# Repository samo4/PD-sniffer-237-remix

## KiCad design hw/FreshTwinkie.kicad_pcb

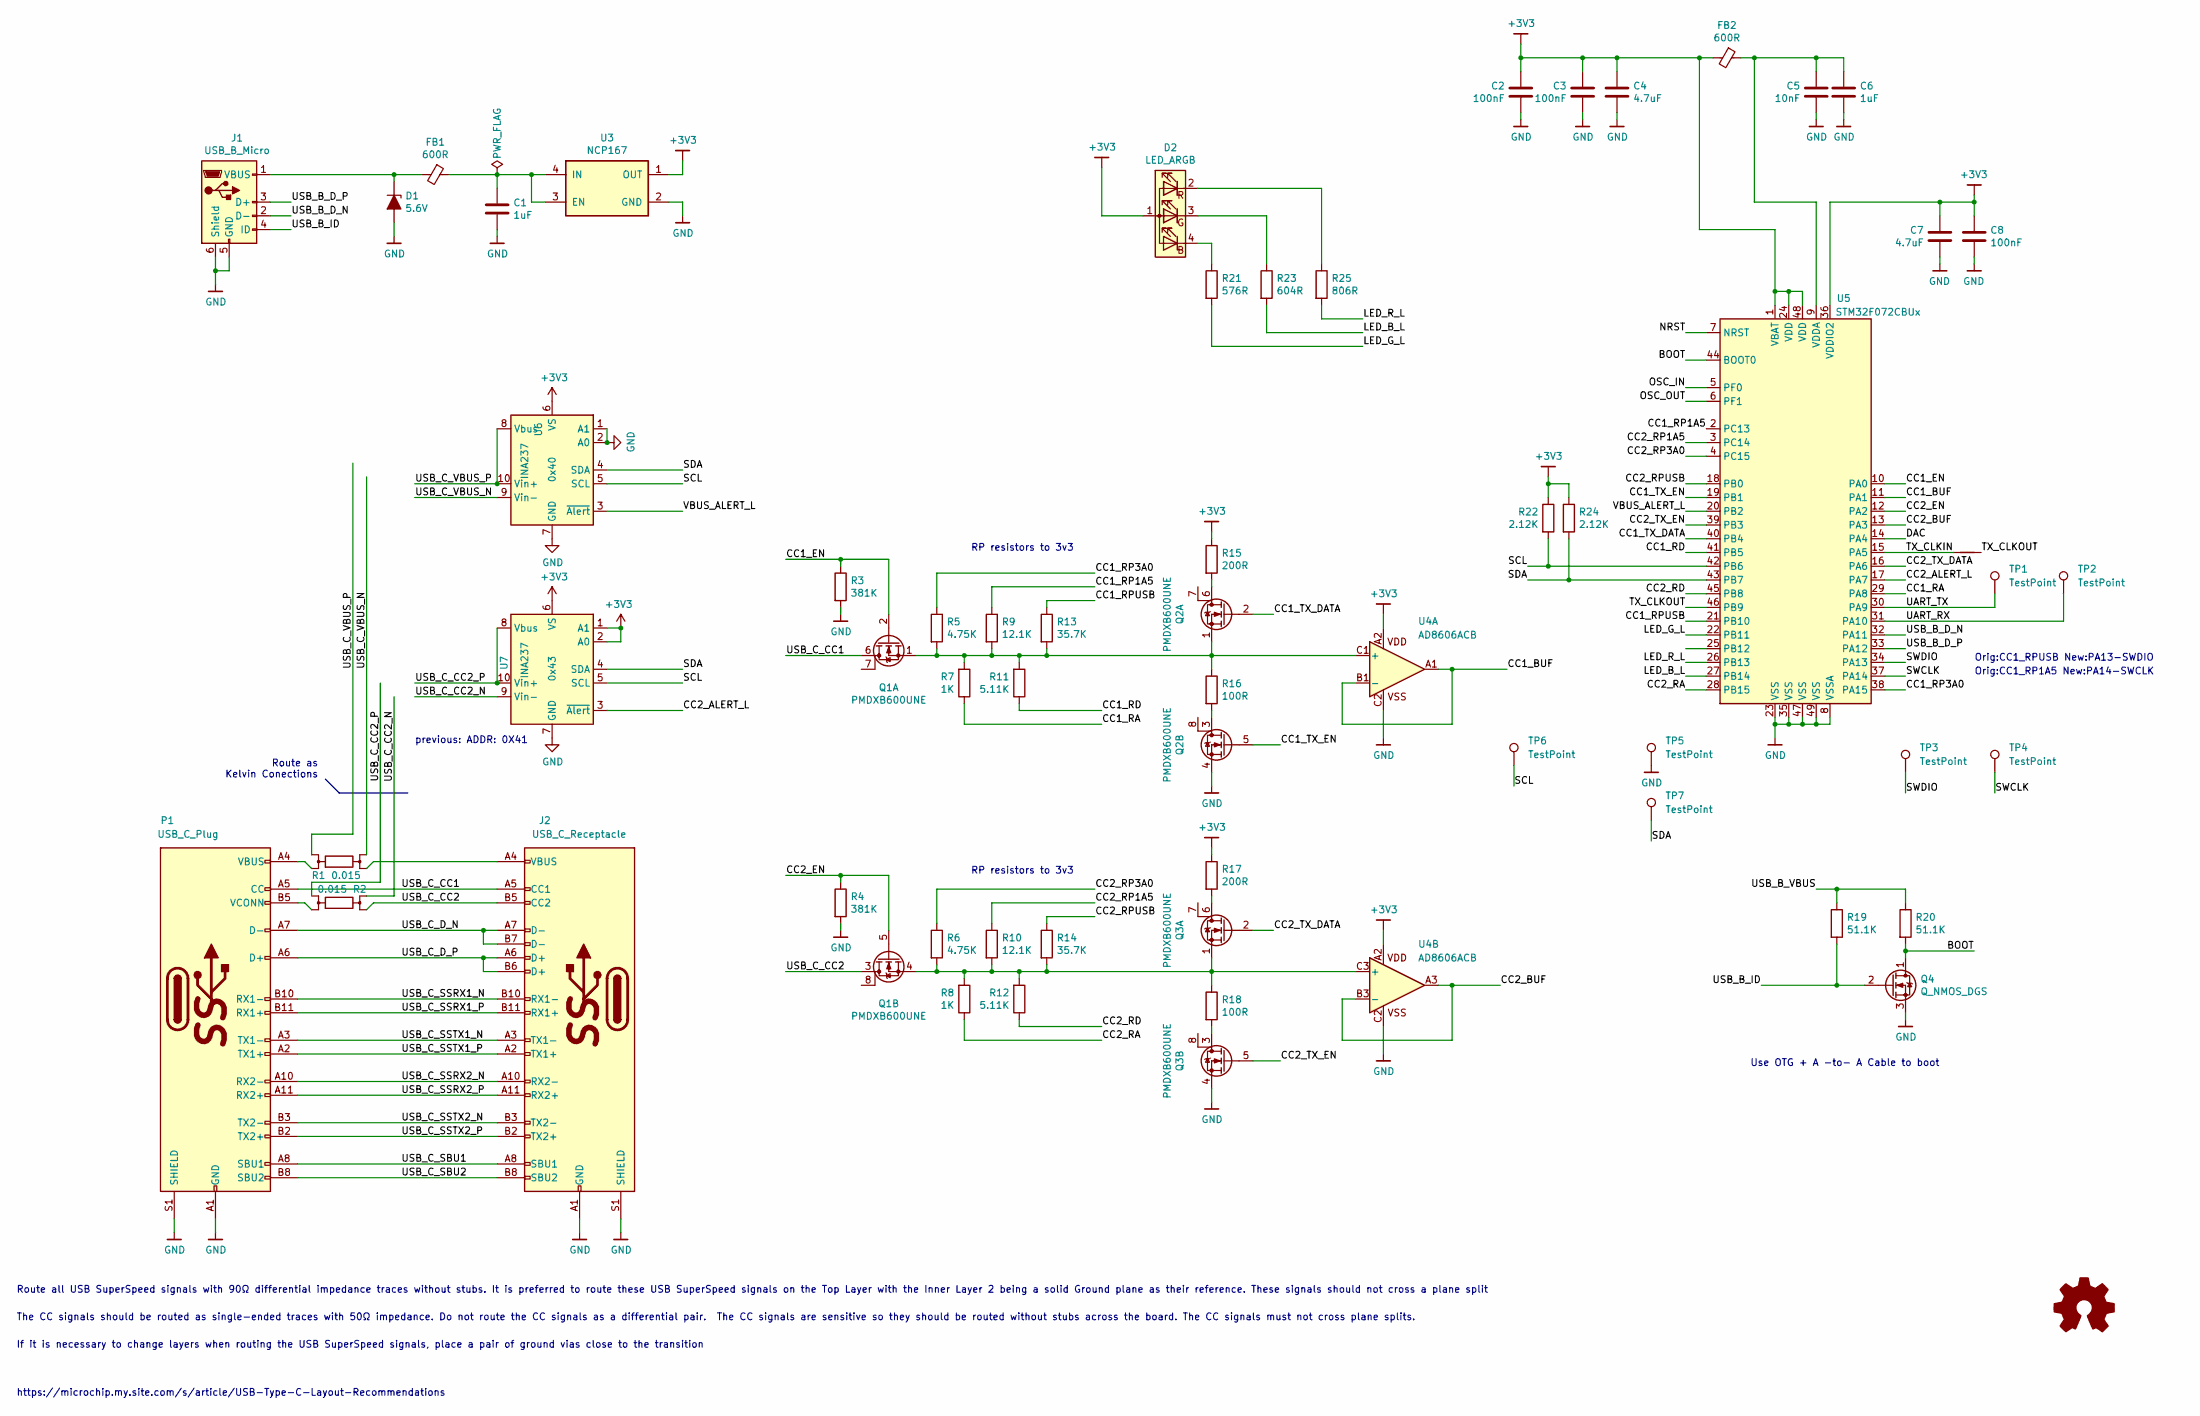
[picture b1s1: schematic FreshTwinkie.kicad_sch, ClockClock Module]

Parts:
C1, C6: 1uF; C_0402
C2, C3, C8: 100nF; C_0201
C4, C7: 4.7uF; C_0402
C5: 10nF; C_0201
D1: 5.6V; D_0402_1005Metric
D2: LED_ARGB; 0404LED_RGB
FB1, FB2: 600R; L_0402
J1: USB_B_Micro; USB_Micro-B_GCT_USB3076-30-A
J2: USB_C_Receptacle; USB_C_Receptacle_Amphenol_12401610E4-2A
NT1: Net-Tie_2; NetTie-2_SMD_Pad0.5mm
P1: USB_C_Plug; USB_C_Plug_Molex_105444
Q1, Q2, Q3: PMDXB600UNE; DFN1010B-6 (SOT1216)
Q4: Q_NMOS_DGS; MOSFET_1.0x0.6mm
R1, R2: 0.015; 4W_R_1206
R3, R4: 381K; R_0201
R5, R6: 4.75K; R_0201
R7, R8: 1K; R_0201
R9, R10: 12.1K; R_0201
R11, R12: 5.11K; R_0201
R13, R14: 35.7K; R_0201
R15, R17: 200R; R_0201
R16, R18: 100R; R_0201
R19, R20: 51.1K; R_0201
R21: 576R; R_0201
R22, R24: 2.12K; R_0201
R23: 604R; R_0201
R25: 806R; R_0201
TP1, TP2, TP3, TP4, TP5, TP6, TP7: TestPoint; TestPoint_Pad_D1.0mm
U3: NCP167; X2SON_4_1.0x1.0mm
U4: AD8606ACB; WLCSP-8 3X3_0.5
U5: STM32F072CBUx; QFN-48-1EP_7x7mm_P0.5mm_EP5.6x5.6mm
U6, U7: INA237; VSSOP-10_3x3mm_P0.5mm; Mfg P/N INA237AIDGSR; DigiKey P/N 296-INA237AIDGSRCT-ND

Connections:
+3V3: C2.1, C3.1, C4.1, C7.1, C8.1, D2.1 (A), FB2.2, R15.1, R17.1, R22.1, R24.1, U3.1 (OUT), U4.A2, U5.1 (VBAT), U5.24 (VDD), U5.36 (VDDIO2), U5.48 (VDD), U6.6 (VS), U7.1 (A1), U7.2 (A0), U7.6 (VS)
/BOOT: Q4.1 (D), R20.2, U5.44 (BOOT0)
/CC1_BUF: U4.A1, U4.B1 (-), U5.11 (PA1)
/CC1_EN: Q1.2 (G), R3.1, U5.10 (PA0)
/CC1_RA: R7.1, U5.29 (PA8)
/CC1_RD: R11.1, U5.41 (PB5)
/CC1_RP1A5: R9.1, U5.2 (PC13)
/CC1_RP3A0: R5.1, U5.38 (PA15)
/CC1_RPUSB: R13.1, U5.21 (PB10)
/CC1_TX_DATA: Q2.2 (G), U5.40 (PB4)
/CC1_TX_EN: Q2.5 (G), U5.19 (PB1)
/CC2_ALERT_L: U5.17 (PA7), U7.3 (~Alert)
/CC2_BUF: U4.A3, U4.B3 (-), U5.13 (PA3)
/CC2_EN: Q1.5 (G), R4.1, U5.12 (PA2)
/CC2_RA: R8.1, U5.28 (PB15)
/CC2_RD: R12.1, U5.45 (PB8)
/CC2_RP1A5: R10.1, U5.3 (PC14)
/CC2_RP3A0: R6.1, U5.4 (PC15)
/CC2_RPUSB: R14.1, U5.18 (PB0)
/CC2_TX_DATA: Q3.2 (G), U5.16 (PA6)
/CC2_TX_EN: Q3.5 (G), U5.39 (PB3)
/DAC: U5.14 (PA4)
/LED_B_L: R23.2, U5.27 (PB14)
/LED_G_L: R21.2, U5.22 (PB11)
/LED_R_L: R25.2, U5.26 (PB13)
/NRST: U5.7 (NRST)
/OSC_IN: U5.5 (PF0)
/OSC_OUT: U5.6 (PF1)
/SCL: R22.2, TP6.1, U5.42 (PB6), U6.5 (SCL), U7.5 (SCL)
/SDA: R24.2, TP7.1, U5.43 (PB7), U6.4 (SDA), U7.4 (SDA)
/SWCLK: TP4.1, U5.37 (PA14)
/SWDIO: TP3.1, U5.34 (PA13)
/TX_CLKIN: NT1.1, U5.15 (PA5)
/TX_CLKOUT: NT1.2, U5.46 (PB9)
/UART_RX: TP2.1, U5.31 (PA10)
/UART_TX: TP1.1, U5.30 (PA9)
/USB_B_D_N: J1.2 (D-), U5.32 (PA11)
/USB_B_D_P: J1.3 (D+), U5.33 (PA12)
/USB_B_ID: J1.4 (ID), Q4.2 (G), R19.2
/USB_B_VBUS: R19.1, R20.1
/USB_C_CC1: J2.A5 (CC1), P1.A5 (CC), Q1.6 (D)
/USB_C_CC2: J2.B5 (CC2), Q1.3 (D), R2.1
/USB_C_CC2_N: R2.3, U7.9 (Vin-)
/USB_C_CC2_P: R2.4, U7.8 (Vbus), U7.10 (Vin+)
/USB_C_D_N: J2.A7 (D-), J2.B7 (D-), P1.A7 (D-)
/USB_C_D_P: J2.A6 (D+), J2.B6 (D+), P1.A6 (D+)
/USB_C_SBU1: J2.A8 (SBU1), P1.A8 (SBU1)
/USB_C_SBU2: J2.B8 (SBU2), P1.B8 (SBU2)
/USB_C_SSRX1_N: J2.B10 (RX1-), P1.B10 (RX1-)
/USB_C_SSRX1_P: J2.B11 (RX1+), P1.B11 (RX1+)
/USB_C_SSRX2_N: J2.A10 (RX2-), P1.A10 (RX2-)
/USB_C_SSRX2_P: J2.A11 (RX2+), P1.A11 (RX2+)
/USB_C_SSTX1_N: J2.A3 (TX1-), P1.A3 (TX1-)
/USB_C_SSTX1_P: J2.A2 (TX1+), P1.A2 (TX1+)
/USB_C_SSTX2_N: J2.B3 (TX2-), P1.B3 (TX2-)
/USB_C_SSTX2_P: J2.B2 (TX2+), P1.B2 (TX2+)
/USB_C_VBUS_N: R1.3, U6.9 (Vin-)
/USB_C_VBUS_P: R1.4, U6.8 (Vbus), U6.10 (Vin+)
/VBUS_ALERT_L: U5.20 (PB2), U6.3 (~Alert)
GND: C1.2, C2.2, C3.2, C4.2, C5.2, C6.2, C7.2, C8.2, D1.2 (A), J1.5 (GND), J1.6 (Shield), J2.A1 (GND), J2.A12 (GND), J2.B1 (GND), J2.B12 (GND), J2.S1 (SHIELD), P1.A1 (GND), P1.A12 (GND), P1.B1 (GND), P1.B12 (GND), P1.S1 (SHIELD), Q2.4 (S), Q3.4 (S), Q4.3 (S), R3.2, R4.2, TP5.1, U3.2 (GND), U4.C2, U5.8 (VSSA), U5.23 (VSS), U5.35 (VSS), U5.47 (VSS), U5.49 (VSS), U6.1 (A1), U6.2 (A0), U6.7 (GND), U7.7 (GND)
unnamed: D1.1 (K), FB1.2, J1.1 (VBUS)
unnamed: D2.4 (BK), R21.1
unnamed: D2.3 (GK), R23.1
unnamed: D2.2 (RK), R25.1
unnamed: J2.A4 (VBUS), J2.A9 (VBUS), J2.B4 (VBUS), J2.B9 (VBUS), R1.1
unnamed: P1.A4 (VBUS), P1.A9 (VBUS), P1.B4 (VBUS), P1.B9 (VBUS), R1.2
unnamed: P1.B5 (VCONN), R2.2
unnamed: Q1.1 (S), Q2.1 (S), R5.2, R7.2, R9.2, R11.2, R13.2, R16.1, U4.C1 (+)
unnamed: Q1.4 (S), Q3.1 (S), R6.2, R8.2, R10.2, R12.2, R14.2, R18.1, U4.C3 (+)
unnamed: Q2.6 (D), R15.2
unnamed: Q2.3 (D), R16.2
unnamed: Q3.6 (D), R17.2
unnamed: Q3.3 (D), R18.2
unnamed: C1.1, FB1.1, U3.3 (EN), U3.4 (IN)
unnamed: C5.1, C6.1, FB2.1, U5.9 (VDDA)

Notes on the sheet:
Orig:CC1_RPUSB New:PA13-SWDIO
Orig:CC1_RP1A5 New:PA14-SWCLK
RP resistors to 3v3
Route as Kelvin Conections
https://microchip.my.site.com/s/article/USB-Type-C-Layout-Recommendations
Use OTG + A -to- A Cable to boot
previous: ADDR: 0X41
The CC signals should be routed as single-ended traces with 50Ω impedance. Do not route the CC signals as a differential pair. The CC signals are sensitive so they should be routed without stubs across the board. The CC signals must not cross plane splits.
Route all USB SuperSpeed signals with 90Ω differential impedance traces without stubs. It is preferred to route these USB SuperSpeed signals on the Top Layer with the Inner Layer 2 being a solid Ground plane as their reference. These signals should not cross a plane split
If it is necessary to change layers when routing the USB SuperSpeed signals, place a pair of ground vias close to the transition

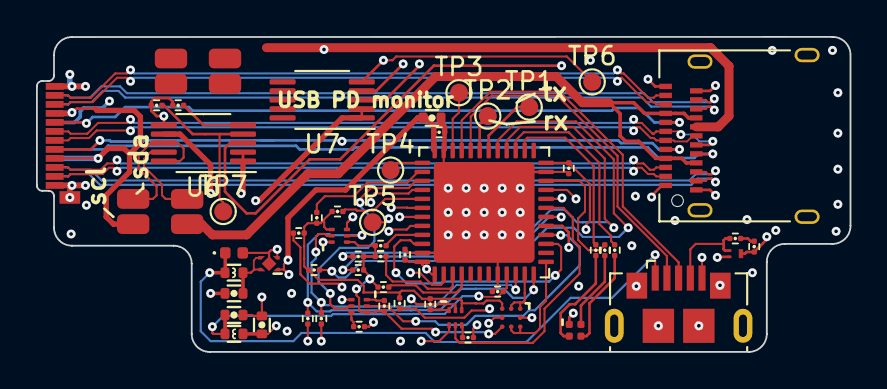
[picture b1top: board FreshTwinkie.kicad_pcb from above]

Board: 6 copper layers, 45.2 x 17.5 mm, 57 parts (1 on the bottom side), 71 nets.

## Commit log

2023-12-08 initial remix
2023-12-09 wip with rules, 6 layer
